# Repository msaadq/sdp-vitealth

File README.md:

# Senior Design Project - Vitealth
This repository contains the complete codebase of Vitealth.

Copyright © VITEALTH 2016. All Rights Reserved.

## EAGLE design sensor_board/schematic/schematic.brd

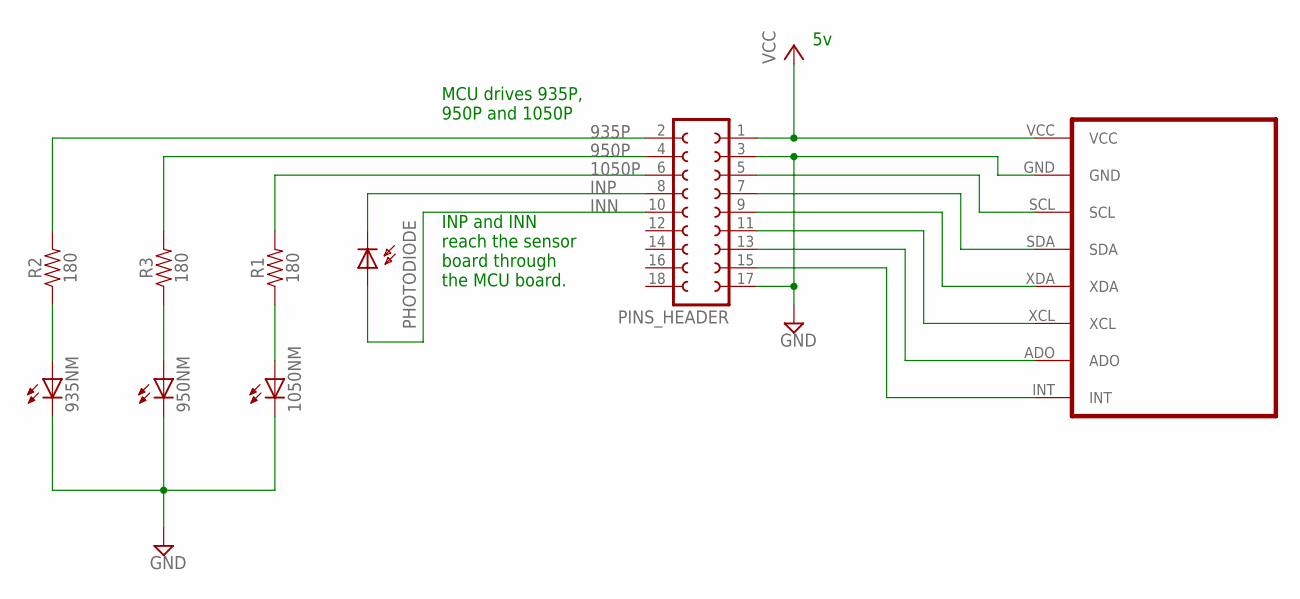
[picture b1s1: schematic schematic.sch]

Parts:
935NM, 950NM: LEDIRL80A; IRL80A
1050NM: LED_E; LED_1206
PHOTODIODE: SFH206
PINS_HEADER: FE09-2
R1, R2, R3: 180; AXIAL-0.3
U1: GY-521MPU6050; GY-521

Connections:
935P: PINS_HEADER.2, R2.P$2 (2)
950P: PINS_HEADER.4, R3.P$2 (2)
1050P: PINS_HEADER.6, R1.P$2 (2)
GND: 935NM.K (C), 950NM.K (C), 1050NM.C, PINS_HEADER.3, PINS_HEADER.17, U1.GND
INN: PHOTODIODE.A, PINS_HEADER.10
INP: PHOTODIODE.K (C), PINS_HEADER.8
unnamed: 1050NM.A, R1.P$1 (1)
unnamed: 935NM.A, R2.P$1 (1)
unnamed: 950NM.A, R3.P$1 (1)
unnamed: PINS_HEADER.5, U1.SCL
unnamed: PINS_HEADER.7, U1.SDA
unnamed: PINS_HEADER.9, U1.XDA
unnamed: PINS_HEADER.11, U1.XCL
unnamed: PINS_HEADER.13, U1.ADO
unnamed: PINS_HEADER.15, U1.INT
VCC: PINS_HEADER.1, U1.VCC

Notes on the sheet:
INP and INN reach the sensor board through the MCU board.
MCU drives 935P, 950P and 1050P

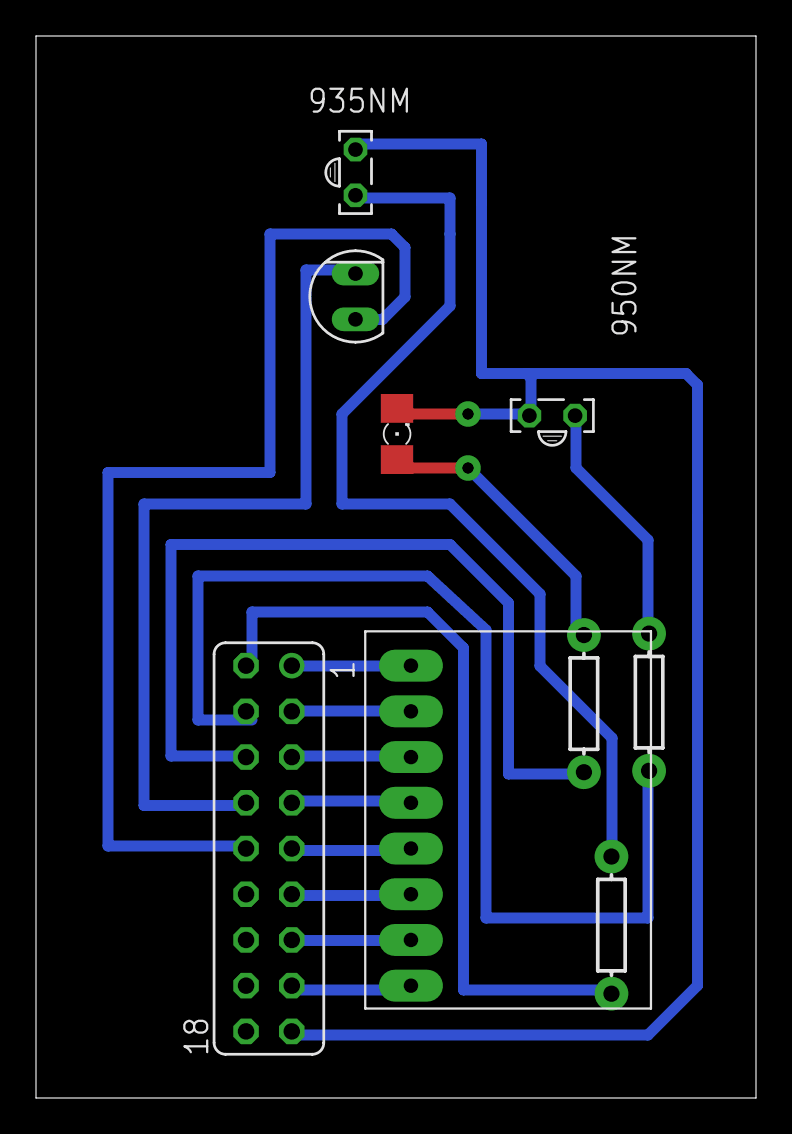
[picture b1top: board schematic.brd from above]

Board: 2 copper layers, 40.0 x 59.0 mm, 9 parts (0 on the bottom side), 16 nets.

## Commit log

2016-12-11 mpu6050 library for AVR microcontroller.
2017-01-31 Adds the configuration file for AFEEVAL GUI
2017-02-25 no message
2017-02-25 Adds the python BGL calc modules
2017-02-25 Creates teh iOS project
2017-02-28 Completes the initial version of the zPortal iOS app
2017-04-08 Adds changes by Javeria
2017-04-11 Adds firebase support
2017-04-11 Fixes the issue with GoogleService-Info.plist file
2017-04-11 Fixes the keyboard issue.
2017-04-11 Adds the training datasets and starter code for adaptive filter.
2017-04-21 Keyboard update, saves to firebase
2017-04-21 Fixes the scroll view constraints
2017-04-23 Complete arduino sketch for led switching with interrupts from the AFE4400 board.
2017-04-25 Takes Patient information and calculates ISF using insulin used yesterday
2017-04-28 Bug fixes to the fetch previous day isf
2017-04-29 Bug fixes to the previous bug fixes
2017-04-30 Allows user to add his own dose if he thinks app recommended dose isn’t accurate
2017-05-03 If user has been inactive for too long, ask him sum of insulin he uses in a day
2017-05-07 Adds the merged project (accelerometer+switching)
2017-05-10 UI partial fixing Takes basal insulin and calculates residual effect
2017-05-14 Profile page incorporated
2017-05-15 User Interface
2017-05-17 Bug fixes
2017-05-17 Test commit
2017-05-18 Adds training data
2017-05-18 Adds graphs
2017-07-01 Adds dataset

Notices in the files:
parts and their libraries:
SparkFun-Resistors: Licensing: Creative Commons ShareAlike 4.0 International - https://creativecommons.org/licenses/by-sa/4.0
